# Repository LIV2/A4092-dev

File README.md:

# A4092

A modern successor to the A4091.

* TSSOP parts for smaller footprint
* Flash instead of EPROM
* CPLD instead of GALs
* Autoconfig moved into CPLD

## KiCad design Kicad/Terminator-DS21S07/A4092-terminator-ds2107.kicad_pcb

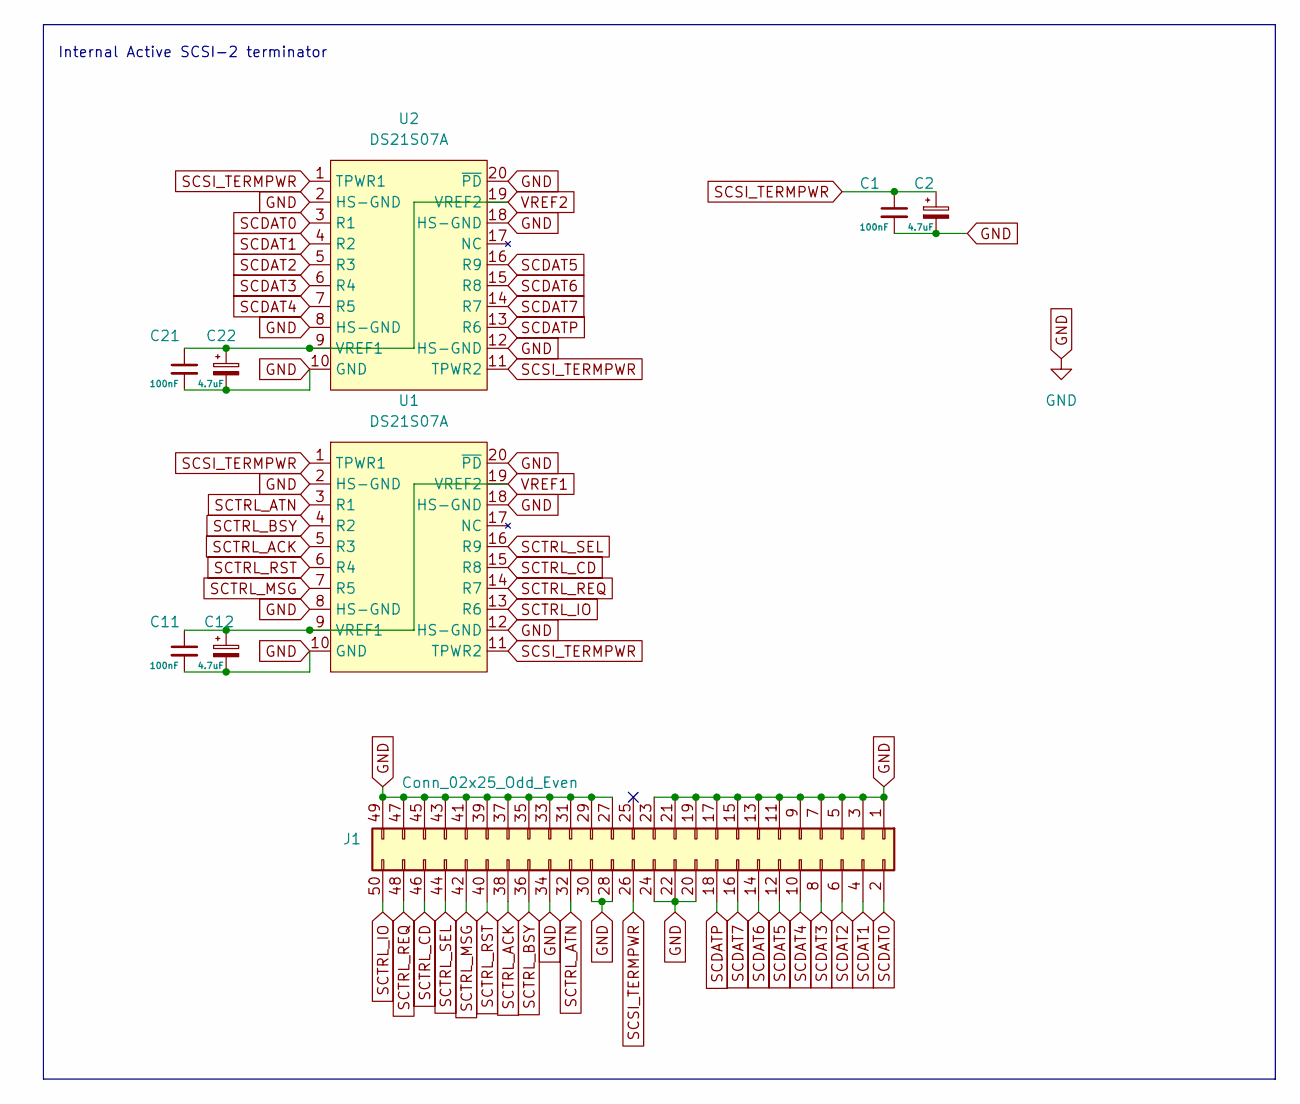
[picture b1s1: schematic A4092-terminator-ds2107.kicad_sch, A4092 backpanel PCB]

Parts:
C1, C11, C21: 100nF; C_0603_1608Metric_Pad1.08x0.95mm_HandSolder; LCSC Part # C14663
C2, C12, C22: 4.7uF; CP_EIA-3216-10_Kemet-I_HandSolder; LCSC Part # C7189
J1: Conn_02x25_Odd_Even; IDC-Header_2x25_P2.54mm_Horizontal; LCSC Part # C7430330
U1, U2: DS21S07A; TSSOP-20_4.4x6.5mm_P0.65mm; LCSC Part # C6602097

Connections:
GND: C1.2, C2.2, C11.2, C12.2, C21.2, C22.2, J1.1, J1.3, J1.5, J1.7, J1.9, J1.11, J1.13, J1.15, J1.17, J1.19, J1.20, J1.21, J1.22, J1.23, J1.24, J1.27, J1.28, J1.29, J1.30, J1.31, J1.33, J1.34, J1.35, J1.37, J1.39, J1.41, J1.43, J1.45, J1.47, J1.49, U1.2 (HS-GND), U1.8 (HS-GND), U1.10 (GND), U1.12 (HS-GND), U1.18 (HS-GND), U1.20 (~PD), U2.2 (HS-GND), U2.8 (HS-GND), U2.10 (GND), U2.12 (HS-GND), U2.18 (HS-GND), U2.20 (~PD)
SCDAT0: J1.2, U2.3 (R1)
SCDAT1: J1.4, U2.4 (R2)
SCDAT2: J1.6, U2.5 (R3)
SCDAT3: J1.8, U2.6 (R4)
SCDAT4: J1.10, U2.7 (R5)
SCDAT5: J1.12, U2.16 (R9)
SCDAT6: J1.14, U2.15 (R8)
SCDAT7: J1.16, U2.14 (R7)
SCDATP: J1.18, U2.13 (R6)
SCSI_TERMPWR: C1.1, C2.1, J1.26, U1.1 (TPWR1), U1.11 (TPWR2), U2.1 (TPWR1), U2.11 (TPWR2)
SCTRL_ACK: J1.38, U1.5 (R3)
SCTRL_ATN: J1.32, U1.3 (R1)
SCTRL_BSY: J1.36, U1.4 (R2)
SCTRL_CD: J1.46, U1.15 (R8)
SCTRL_IO: J1.50, U1.13 (R6)
SCTRL_MSG: J1.42, U1.7 (R5)
SCTRL_REQ: J1.48, U1.14 (R7)
SCTRL_RST: J1.40, U1.6 (R4)
SCTRL_SEL: J1.44, U1.16 (R9)
VREF1: C11.1, C12.1, U1.9 (VREF1), U1.19 (VREF2)
VREF2: C21.1, C22.1, U2.9 (VREF1), U2.19 (VREF2)

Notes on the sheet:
Internal Active SCSI-2 terminator

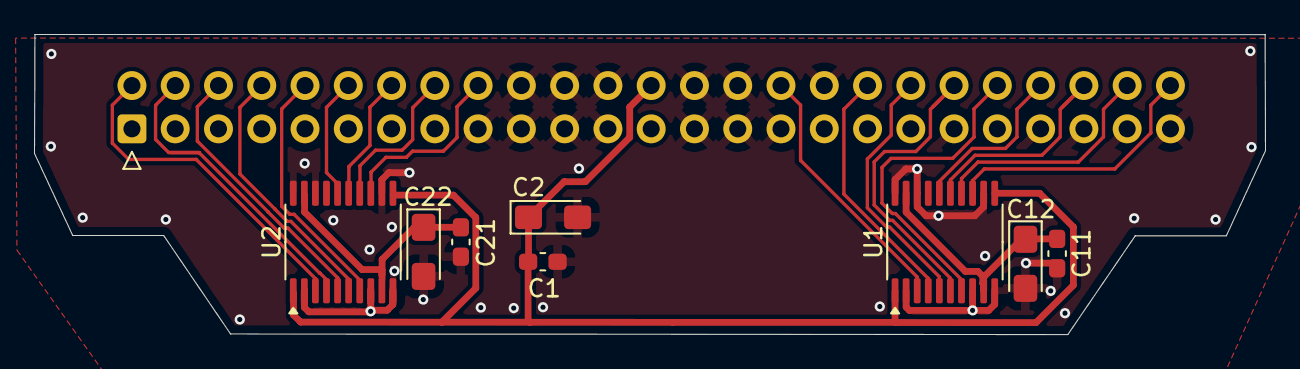
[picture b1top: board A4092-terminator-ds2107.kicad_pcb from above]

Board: 2 copper layers, 72.3 x 17.6 mm, 9 parts (0 on the bottom side), 22 nets.

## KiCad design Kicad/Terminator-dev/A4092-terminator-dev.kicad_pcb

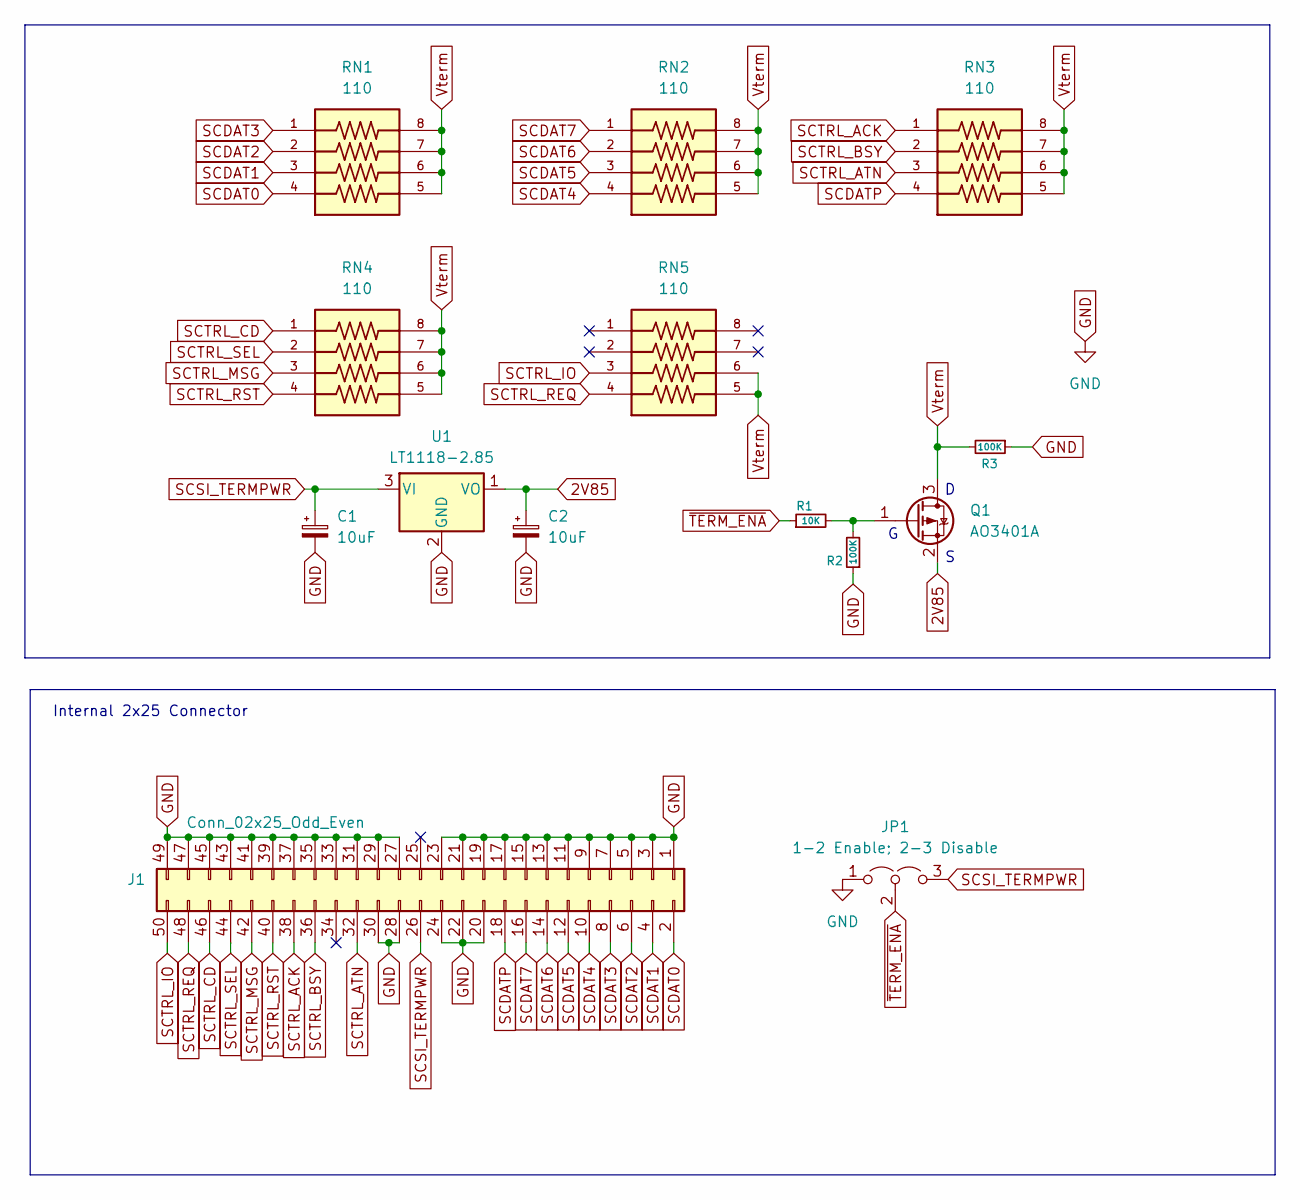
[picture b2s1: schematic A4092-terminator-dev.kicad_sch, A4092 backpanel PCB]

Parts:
C1, C2: 10uF; CP_EIA-2012-12_Kemet-R; LCSC Part # C7171
J1: Conn_02x25_Odd_Even; IDC-Header_2x25_P2.54mm_Horizontal; LCSC Part # C7430330
JP1: 1-2 Enable; 2-3 Disable; PinHeader_1x03_P2.00mm_Horizontal
Q1: AO3401A; SOT-23
R1: 10K; R_0603_1608Metric
R2, R3: 100K; R_0603_1608Metric
RN1, RN2, RN3, RN4, RN5: 110; BO_CAY16; PARTREV V.9; LCSC Part # C176176
U1: LT1118-2.85; SOT-223-3_TabPin2; LCSC Part # C2870974

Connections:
2V85: C2.1, Q1.2 (S), U1.1 (VO)
GND: C1.2, C2.2, J1.1, J1.3, J1.5, J1.7, J1.9, J1.11, J1.13, J1.15, J1.17, J1.19, J1.20, J1.21, J1.22, J1.23, J1.24, J1.27, J1.28, J1.29, J1.30, J1.31, J1.33, J1.35, J1.37, J1.39, J1.41, J1.43, J1.45, J1.47, J1.49, JP1.1 (A), R2.1, R3.1, U1.2 (GND)
unnamed: Q1.1 (G), R1.2, R2.2
SCDAT0: J1.2, RN1.4
SCDAT1: J1.4, RN1.3
SCDAT2: J1.6, RN1.2
SCDAT3: J1.8, RN1.1
SCDAT4: J1.10, RN2.4
SCDAT5: J1.12, RN2.3
SCDAT6: J1.14, RN2.2
SCDAT7: J1.16, RN2.1
SCDATP: J1.18, RN3.4
SCSI_TERMPWR: C1.1, J1.26, JP1.3 (B), U1.3 (VI)
SCTRL_ACK: J1.38, RN3.1
SCTRL_ATN: J1.32, RN3.3
SCTRL_BSY: J1.36, RN3.2
SCTRL_CD: J1.46, RN4.1
SCTRL_IO: J1.50, RN5.3
SCTRL_MSG: J1.42, RN4.3
SCTRL_REQ: J1.48, RN5.4
SCTRL_RST: J1.40, RN4.4
SCTRL_SEL: J1.44, RN4.2
Vterm: Q1.3 (D), R3.2, RN1.5, RN1.6, RN1.7, RN1.8, RN2.5, RN2.6, RN2.7, RN2.8, RN3.5, RN3.6, RN3.7, RN3.8, RN4.5, RN4.6, RN4.7, RN4.8, RN5.5, RN5.6
~TERM_ENA: JP1.2 (C), R1.1

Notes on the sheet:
Internal 2x25 Connector

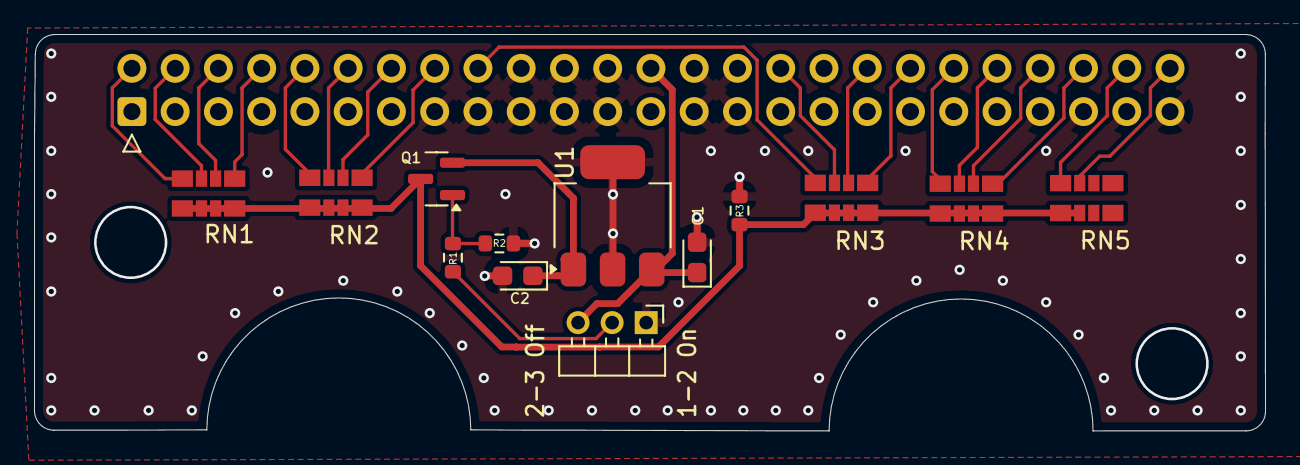
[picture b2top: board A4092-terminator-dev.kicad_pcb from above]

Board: 2 copper layers, 72.3 x 23.3 mm, 14 parts (0 on the bottom side), 24 nets.

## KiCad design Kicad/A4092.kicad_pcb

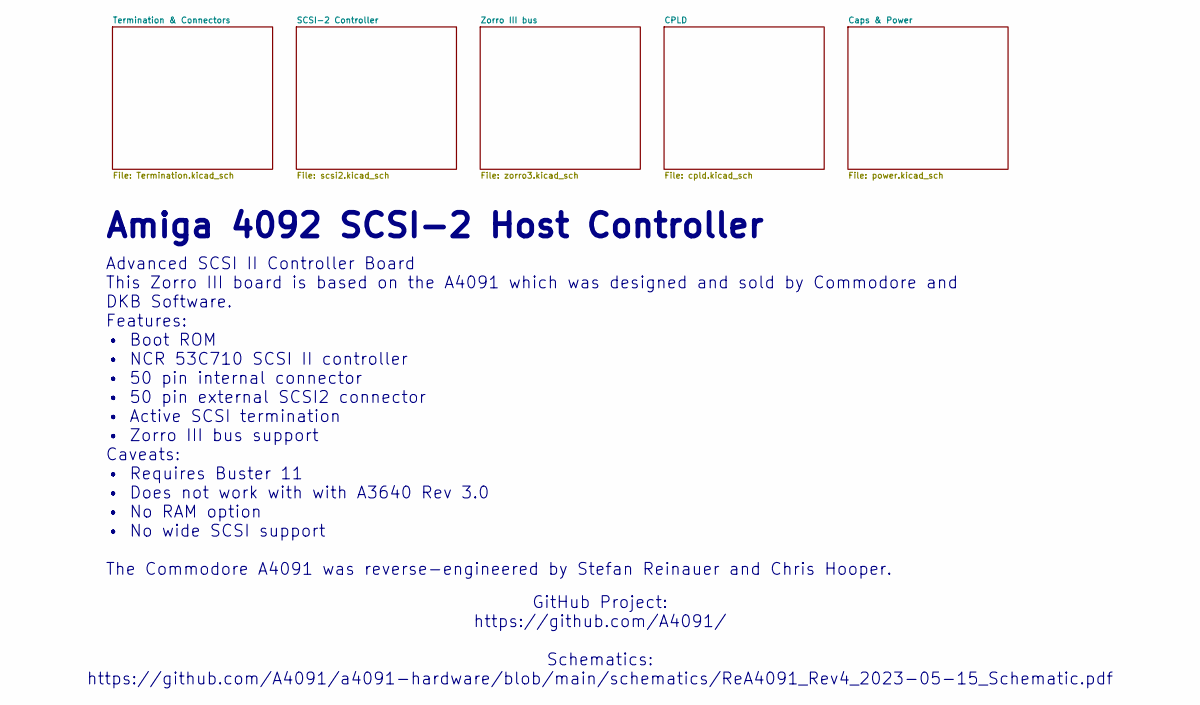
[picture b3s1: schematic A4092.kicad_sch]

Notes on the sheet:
Advanced SCSI II Controller Board This Zorro III board is based on the A4091 which was designed and sold by Commodore and DKB Software. Features: • Boot ROM • NCR 53C710 SCSI II controller • 50 pin internal connector • 50 pin external SCSI2 connector • Active SCSI termination • Zorro III bus suppor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
GitHub Project: https://github.com/A4091/ Schematics: https://github.com/A4091/a4091-hardware/blob/main/schematics/ReA4091_Rev4_2023-05-15_Schematic.pdf
Amiga 4092 SCSI-2 Host Controller

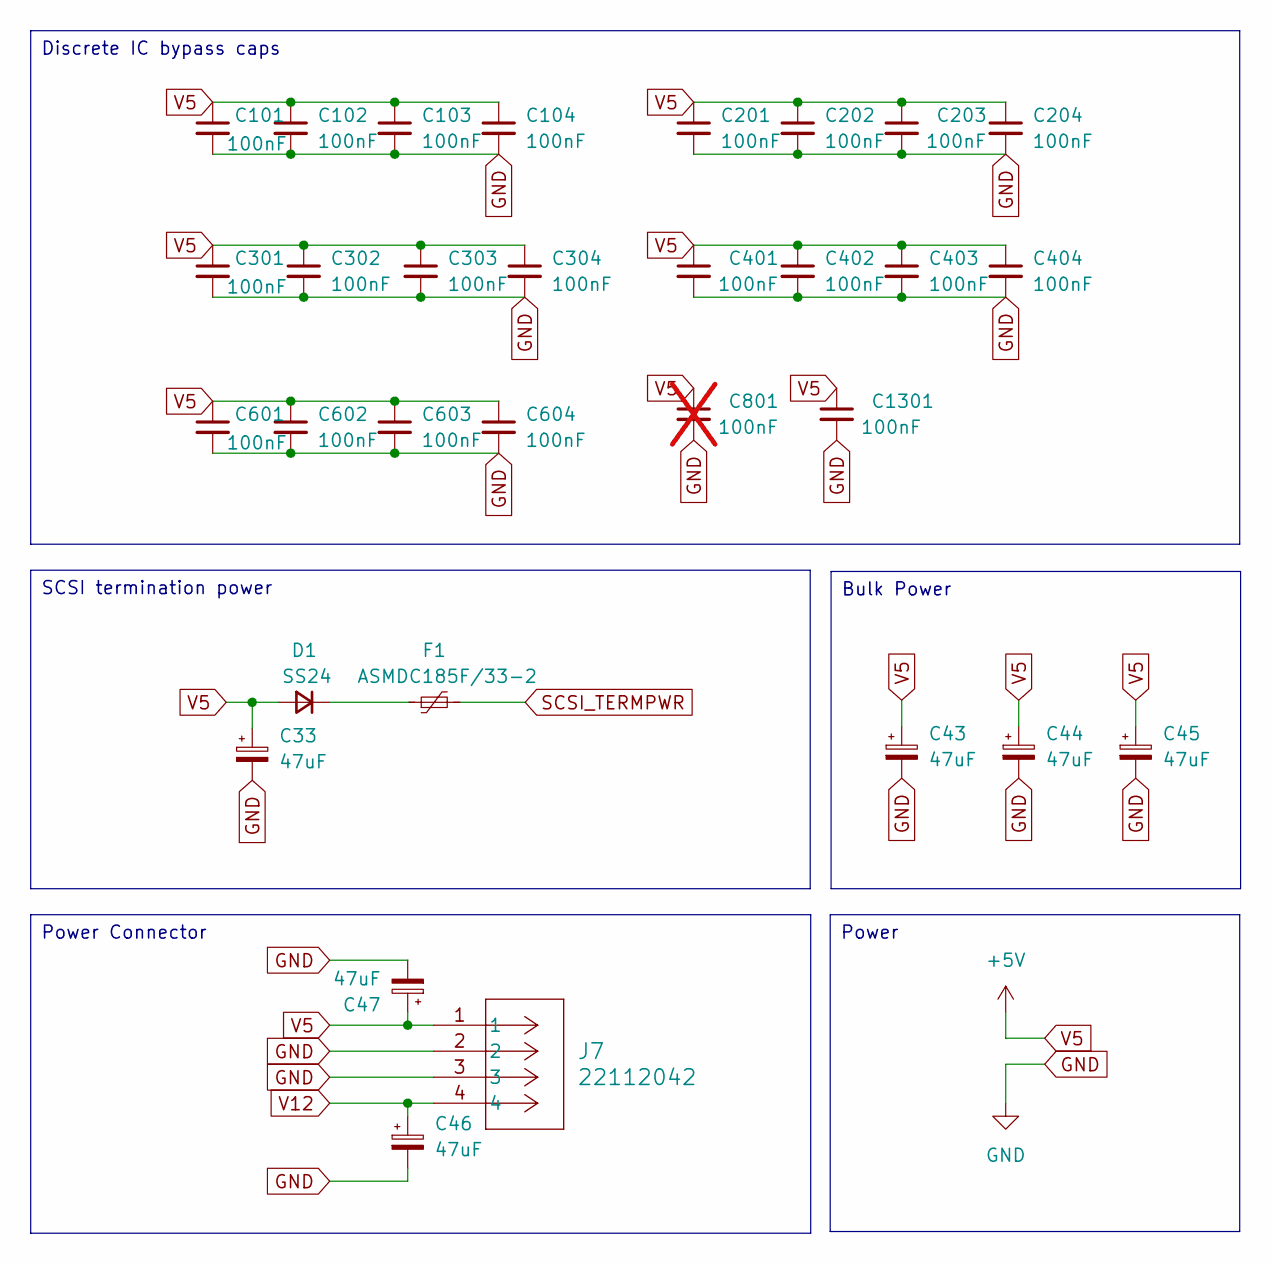
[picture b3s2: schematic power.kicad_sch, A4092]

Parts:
C33, C43, C44, C45, C46, C47: 47uF; CP_Elec_6.3x7.7; MPN KEMET/A765EB476M1ELAE040; LCSC Part # C369909
C101, C102, C103, C104, C201, C202, C203, C204, C301, C302, C303, C304, C401, C402, C403, C404, C601, C602, C603, C604, C1301: 100nF; C_0603_1608Metric_Pad1.08x0.95mm_HandSolder; LCSC Part # C14663
C801: 100nF; C_0603_1608Metric_Pad1.08x0.95mm_HandSolder; LCSC Part # C14663; not fitted
D1: SS24; D_SMA_Handsoldering; LCSC Part # C43381
F1: ASMDC185F/33-2; Fuse_2920_7451Metric_Pad2.10x5.45mm_HandSolder; LCSC Part # C135379
J7: 22112042; CONN_A-6373-04A_MOL; LCSC Part # C114123

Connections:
GND: C33.2, C43.2, C44.2, C45.2, C46.2, C47.2, C101.2, C102.2, C103.2, C104.2, C201.2, C202.2, C203.2, C204.2, C301.2, C302.2, C303.2, C304.2, C401.2, C402.2, C403.2, C404.2, C601.2, C602.2, C603.2, C604.2, C801.2, C1301.2, J7.2, J7.3; also elsewhere on the board
unnamed: D1.1 (K), F1.1
SCSI_TERMPWR: F1.2; also elsewhere on the board
V5: C33.1, C43.1, C44.1, C45.1, C47.1, C101.1, C102.1, C103.1, C104.1, C201.1, C202.1, C203.1, C204.1, C301.1, C302.1, C303.1, C304.1, C401.1, C402.1, C403.1, C404.1, C601.1, C602.1, C603.1, C604.1, C801.1, C1301.1, D1.2 (A), J7.1; also elsewhere on the board
V12: C46.1, J7.4; also elsewhere on the board

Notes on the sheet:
SCSI termination power
Power Connector
Discrete IC bypass caps
Bulk Power
Power

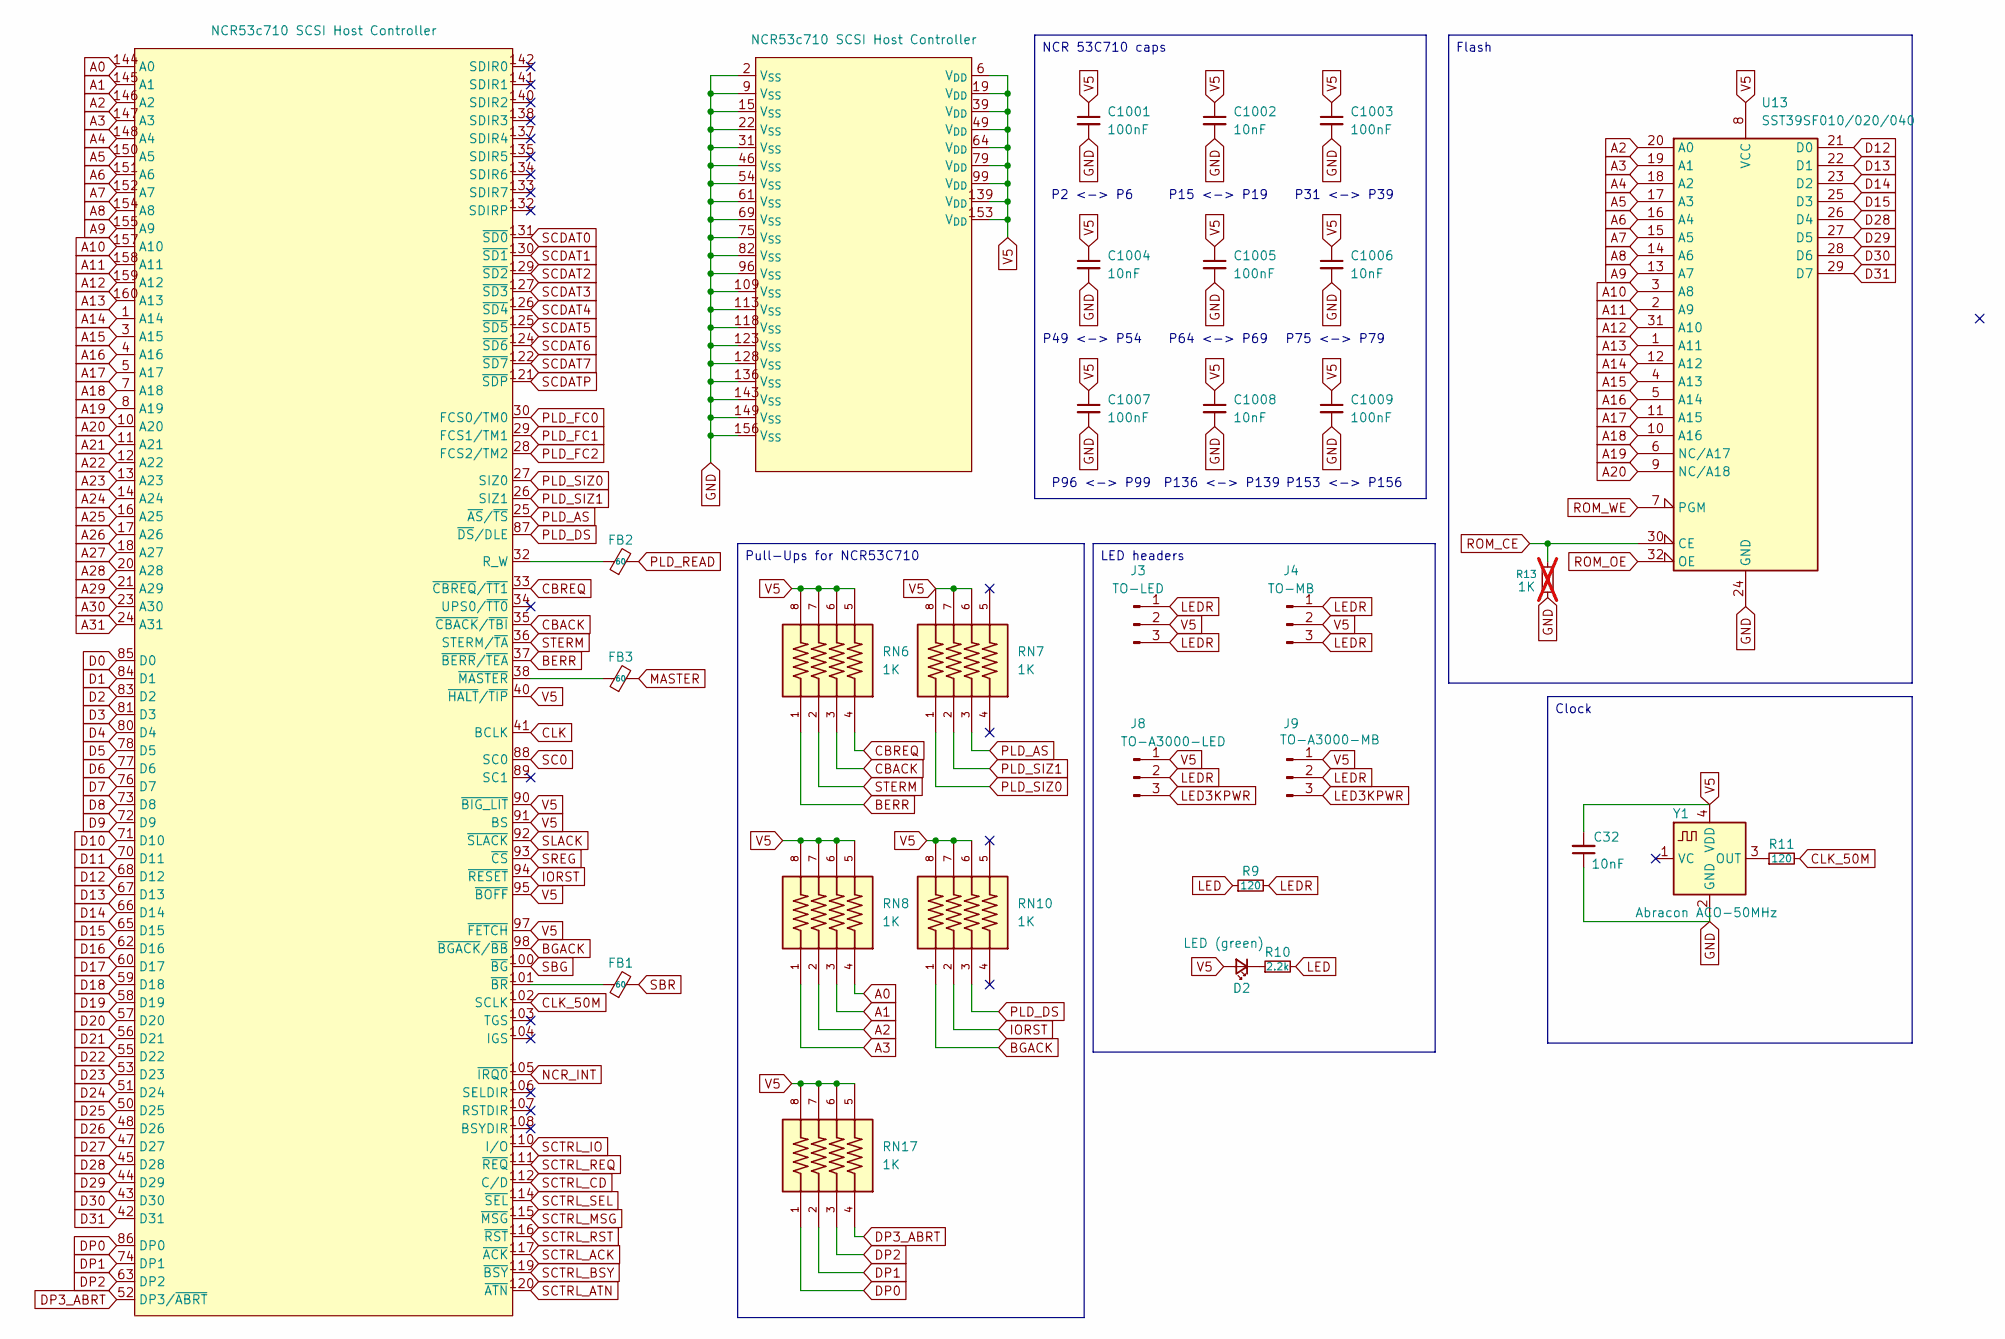
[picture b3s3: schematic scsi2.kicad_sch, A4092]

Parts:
C32, C1002, C1004, C1006, C1008: 10nF; C_0603_1608Metric_Pad1.08x0.95mm_HandSolder; LCSC Part # C100042
C1001, C1003, C1005, C1007, C1009: 100nF; C_0603_1608Metric_Pad1.08x0.95mm_HandSolder; LCSC Part # C14663
D2: LED (green); LED_0805_2012Metric; LCSC Part # C965821
FB1, FB2, FB3: 60; C_0603_1608Metric_Pad1.08x0.95mm_HandSolder; LCSC Part # C95177
J3: TO-LED; PinHeader_1x03_P2.54mm_Vertical; LCSC Part # C6332196
J4: TO-MB; PinHeader_1x03_P2.54mm_Vertical; LCSC Part # C6332196
J8: TO-A3000-LED; PinHeader_1x03_P2.54mm_Vertical; LCSC Part # C6332196
J9: TO-A3000-MB; PinHeader_1x03_P2.54mm_Vertical; LCSC Part # C6332196
R9: 120; R_0603_1608Metric; LCSC Part # C114640
R10: 2.2k; R_0603_1608Metric; LCSC Part # C114662
R11: 120; R_0603_1608Metric; LCSC Part # C95177
R13: 1K; R_0603_1608Metric; LCSC Part # C22548; not fitted
RN6, RN7, RN8, RN10, RN17: 1K; BO_CAY16; PARTREV V.9; LCSC Part # C784824
U10: NCR53c710 SCSI Host Controller; PQFP-160_28x28mm_P0.65mm; LCSC Part # C9900133089
U13: SST39SF010/020/040; TSSOP-32_8x11mm_P0.65mm; LCSC Part # C630569
Y1: Abracon ACO-50MHz; Oscillator_SMD_Fox_FT5H_5.0x3.2mm; LCSC Part # C7431196

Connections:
A0: RN8.4, U10.144 (A0); also elsewhere on the board
A1: RN8.3, U10.145 (A1); also elsewhere on the board
A2: RN8.2, U10.146 (A2), U13.20 (A0); also elsewhere on the board
A3: RN8.1, U10.147 (A3), U13.19 (A1); also elsewhere on the board
A4: U10.148 (A4), U13.18 (A2); also elsewhere on the board
A5: U10.150 (A5), U13.17 (A3); also elsewhere on the board
A6: U10.151 (A6), U13.16 (A4); also elsewhere on the board
A7: U10.152 (A7), U13.15 (A5); also elsewhere on the board
A8: U10.154 (A8), U13.14 (A6); also elsewhere on the board
A9: U10.155 (A9), U13.13 (A7); also elsewhere on the board
A10: U10.157 (A10), U13.3 (A8); also elsewhere on the board
A11: U10.158 (A11), U13.2 (A9); also elsewhere on the board
A12: U10.159 (A12), U13.31 (A10); also elsewhere on the board
A13: U10.160 (A13), U13.1 (A11); also elsewhere on the board
A14: U10.1 (A14), U13.12 (A12); also elsewhere on the board
A15: U10.3 (A15), U13.4 (A13); also elsewhere on the board
A16: U10.4 (A16), U13.5 (A14); also elsewhere on the board
A17: U10.5 (A17), U13.11 (A15); also elsewhere on the board
A18: U10.7 (A18), U13.10 (A16); also elsewhere on the board
A19: U10.8 (A19), U13.6 (NC/A17); also elsewhere on the board
A20: U10.10 (A20), U13.9 (NC/A18); also elsewhere on the board
A21: U10.11 (A21); also elsewhere on the board
A22: U10.12 (A22); also elsewhere on the board
A23: U10.13 (A23); also elsewhere on the board
A24: U10.14 (A24); also elsewhere on the board
A25: U10.16 (A25); also elsewhere on the board
A26: U10.17 (A26); also elsewhere on the board
A27: U10.18 (A27); also elsewhere on the board
A28: U10.20 (A28); also elsewhere on the board
A29: U10.21 (A29); also elsewhere on the board
A30: U10.23 (A30); also elsewhere on the board
A31: U10.24 (A31); also elsewhere on the board
BERR: RN6.1, U10.37 (~BERR/~TEA); also elsewhere on the board
BGACK: RN10.1, U10.98 (~BGACK/~BB)
CBACK: RN6.3, U10.35 (~CBACK/~TBI); also elsewhere on the board
CBREQ: RN6.4, U10.33 (~CBREQ/~TT1); also elsewhere on the board
CLK: U10.41 (BCLK); also elsewhere on the board
CLK_50M: R11.2, U10.102 (SCLK); also elsewhere on the board
D0: U10.85 (D0); also elsewhere on the board
D1: U10.84 (D1); also elsewhere on the board
D2: U10.83 (D2); also elsewhere on the board
D3: U10.81 (D3); also elsewhere on the board
D4: U10.80 (D4); also elsewhere on the board
D5: U10.78 (D5); also elsewhere on the board
D6: U10.77 (D6); also elsewhere on the board
D7: U10.76 (D7); also elsewhere on the board
D8: U10.73 (D8); also elsewhere on the board
D9: U10.72 (D9); also elsewhere on the board
D10: U10.71 (D10); also elsewhere on the board
D11: U10.70 (D11); also elsewhere on the board
D12: U10.68 (D12), U13.21 (D0); also elsewhere on the board
D13: U10.67 (D13), U13.22 (D1); also elsewhere on the board
D14: U10.66 (D14), U13.23 (D2); also elsewhere on the board
D15: U10.65 (D15), U13.25 (D3); also elsewhere on the board
D16: U10.62 (D16); also elsewhere on the board
D17: U10.60 (D17); also elsewhere on the board
D18: U10.59 (D18); also elsewhere on the board
D19: U10.58 (D19); also elsewhere on the board
D20: U10.57 (D20); also elsewhere on the board
D21: U10.56 (D21); also elsewhere on the board
D22: U10.55 (D22); also elsewhere on the board
D23: U10.53 (D23); also elsewhere on the board
D24: U10.51 (D24); also elsewhere on the board
D25: U10.50 (D25); also elsewhere on the board
D26: U10.48 (D26); also elsewhere on the board
D27: U10.47 (D27); also elsewhere on the board
D28: U10.45 (D28), U13.26 (D4); also elsewhere on the board
D29: U10.44 (D29), U13.27 (D5); also elsewhere on the board
D30: U10.43 (D30), U13.28 (D6); also elsewhere on the board
D31: U10.42 (D31), U13.29 (D7); also elsewhere on the board
DP0: RN17.1, U10.86 (DP0)
DP1: RN17.2, U10.74 (DP1)
DP2: RN17.3, U10.63 (DP2)
DP3_ABRT: RN17.4, U10.52 (DP3/~ABRT)
GND: C32.1, C1001.2, C1002.2, C1003.2, C1004.2, C1005.2, C1006.2, C1007.2, C1008.2, C1009.2, R13.2, U10.2 (V_{SS}), U10.9 (V_{SS}), U10.15 (V_{SS}), U10.22 (V_{SS}), U10.31 (V_{SS}), U10.46 (V_{SS}), U10.54 (V_{SS}), U10.61 (V_{SS}), U10.69 (V_{SS}), U10.75 (V_{SS}), U10.82 (V_{SS}), U10.96 (V_{SS}), U10.109 (V_{SS}), U10.113 (V_{SS}), U10.118 (V_{SS}), U10.123 (V_{SS}), U10.128 (V_{SS}), U10.136 (V_{SS}), U10.143 (V_{SS}), U10.149 (V_{SS}), U10.156 (V_{SS}), U13.24 (GND), Y1.2 (GND); also elsewhere on the board
IORST: RN10.2, U10.94 (~RESET); also elsewhere on the board
LED: R9.1, R10.2; also elsewhere on the board
LED3KPWR: J8.3, J9.3
LEDR: J3.1, J3.3, J4.1, J4.3, J8.2, J9.2, R9.2
MASTER: FB3.2; also elsewhere on the board
NCR_INT: U10.105 (~IRQ0); also elsewhere on the board
unnamed: D2.1 (K), R10.1
unnamed: FB2.1, U10.32 (R_W)
unnamed: FB1.1, U10.101 (~BR)
unnamed: FB3.1, U10.38 (~MASTER)
unnamed: R11.1, Y1.3 (OUT)
PLD_AS: RN7.3, U10.25 (~AS/~TS); also elsewhere on the board
PLD_DS: RN10.3, U10.87 (~DS/DLE); also elsewhere on the board
PLD_FC0: U10.30 (FCS0/TM0); also elsewhere on the board
PLD_FC1: U10.29 (FCS1/TM1); also elsewhere on the board
PLD_FC2: U10.28 (FCS2/TM2); also elsewhere on the board
PLD_READ: FB2.2; also elsewhere on the board
PLD_SIZ0: RN7.1, U10.27 (SIZ0); also elsewhere on the board
PLD_SIZ1: RN7.2, U10.26 (SIZ1); also elsewhere on the board
ROM_CE: R13.1, U13.30 (CE); also elsewhere on the board
ROM_OE: U13.32 (OE); also elsewhere on the board
ROM_WE: U13.7 (PGM); also elsewhere on the board
SBG: U10.100 (~BG); also elsewhere on the board
SBR: FB1.2; also elsewhere on the board
SC0: U10.88 (SC0); also elsewhere on the board
SCDAT0: U10.131 (~SD0); also elsewhere on the board
SCDAT1: U10.130 (~SD1); also elsewhere on the board
SCDAT2: U10.129 (~SD2); also elsewhere on the board
SCDAT3: U10.127 (~SD3); also elsewhere on the board
SCDAT4: U10.126 (~SD4); also elsewhere on the board
SCDAT5: U10.125 (~SD5); also elsewhere on the board
SCDAT6: U10.124 (~SD6); also elsewhere on the board
SCDAT7: U10.122 (~SD7); also elsewhere on the board
SCDATP: U10.121 (~SDP); also elsewhere on the board
SCTRL_ACK: U10.117 (~ACK); also elsewhere on the board
SCTRL_ATN: U10.120 (~ATN); also elsewhere on the board
SCTRL_BSY: U10.119 (~BSY); also elsewhere on the board
SCTRL_CD: U10.112 (C/D); also elsewhere on the board
SCTRL_IO: U10.110 (I/O); also elsewhere on the board
SCTRL_MSG: U10.115 (~MSG); also elsewhere on the board
SCTRL_REQ: U10.111 (~REQ); also elsewhere on the board
SCTRL_RST: U10.116 (~RST); also elsewhere on the board
SCTRL_SEL: U10.114 (~SEL); also elsewhere on the board
SLACK: U10.92 (~SLACK); also elsewhere on the board
SREG: U10.93 (~CS); also elsewhere on the board
STERM: RN6.2, U10.36 (STERM/~TA); also elsewhere on the board
V5: C32.2, C1001.1, C1002.1, C1003.1, C1004.1, C1005.1, C1006.1, C1007.1, C1008.1, C1009.1, D2.2 (A), J3.2, J4.2, J8.1, J9.1, RN6.5, RN6.6, RN6.7, RN6.8, RN7.6, RN7.7, RN7.8, RN8.5, RN8.6, RN8.7, RN8.8, RN10.6, RN10.7, RN10.8, RN17.5, RN17.6, RN17.7, RN17.8, U10.6 (V_{DD}), U10.19 (V_{DD}), U10.39 (V_{DD}), U10.40 (~HALT/~TIP), U10.49 (V_{DD}), U10.64 (V_{DD}), U10.79 (V_{DD}), U10.90 (~BIG_LIT), U10.91 (BS), U10.95 (~BOFF), U10.97 (~FETCH), U10.99 (V_{DD}), U10.139 (V_{DD}), U10.153 (V_{DD}), U13.8 (VCC), Y1.4 (VDD); also elsewhere on the board

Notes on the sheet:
P2 <-> P6
P96 <-> P99
P49 <-> P54
P136 <-> P139
P153 <-> P156
P31 <-> P39
P64 <-> P69
P15 <-> P19
P75 <-> P79
LED headers
NCR 53C710 caps
Clock
Flash
Pull-Ups for NCR53C710

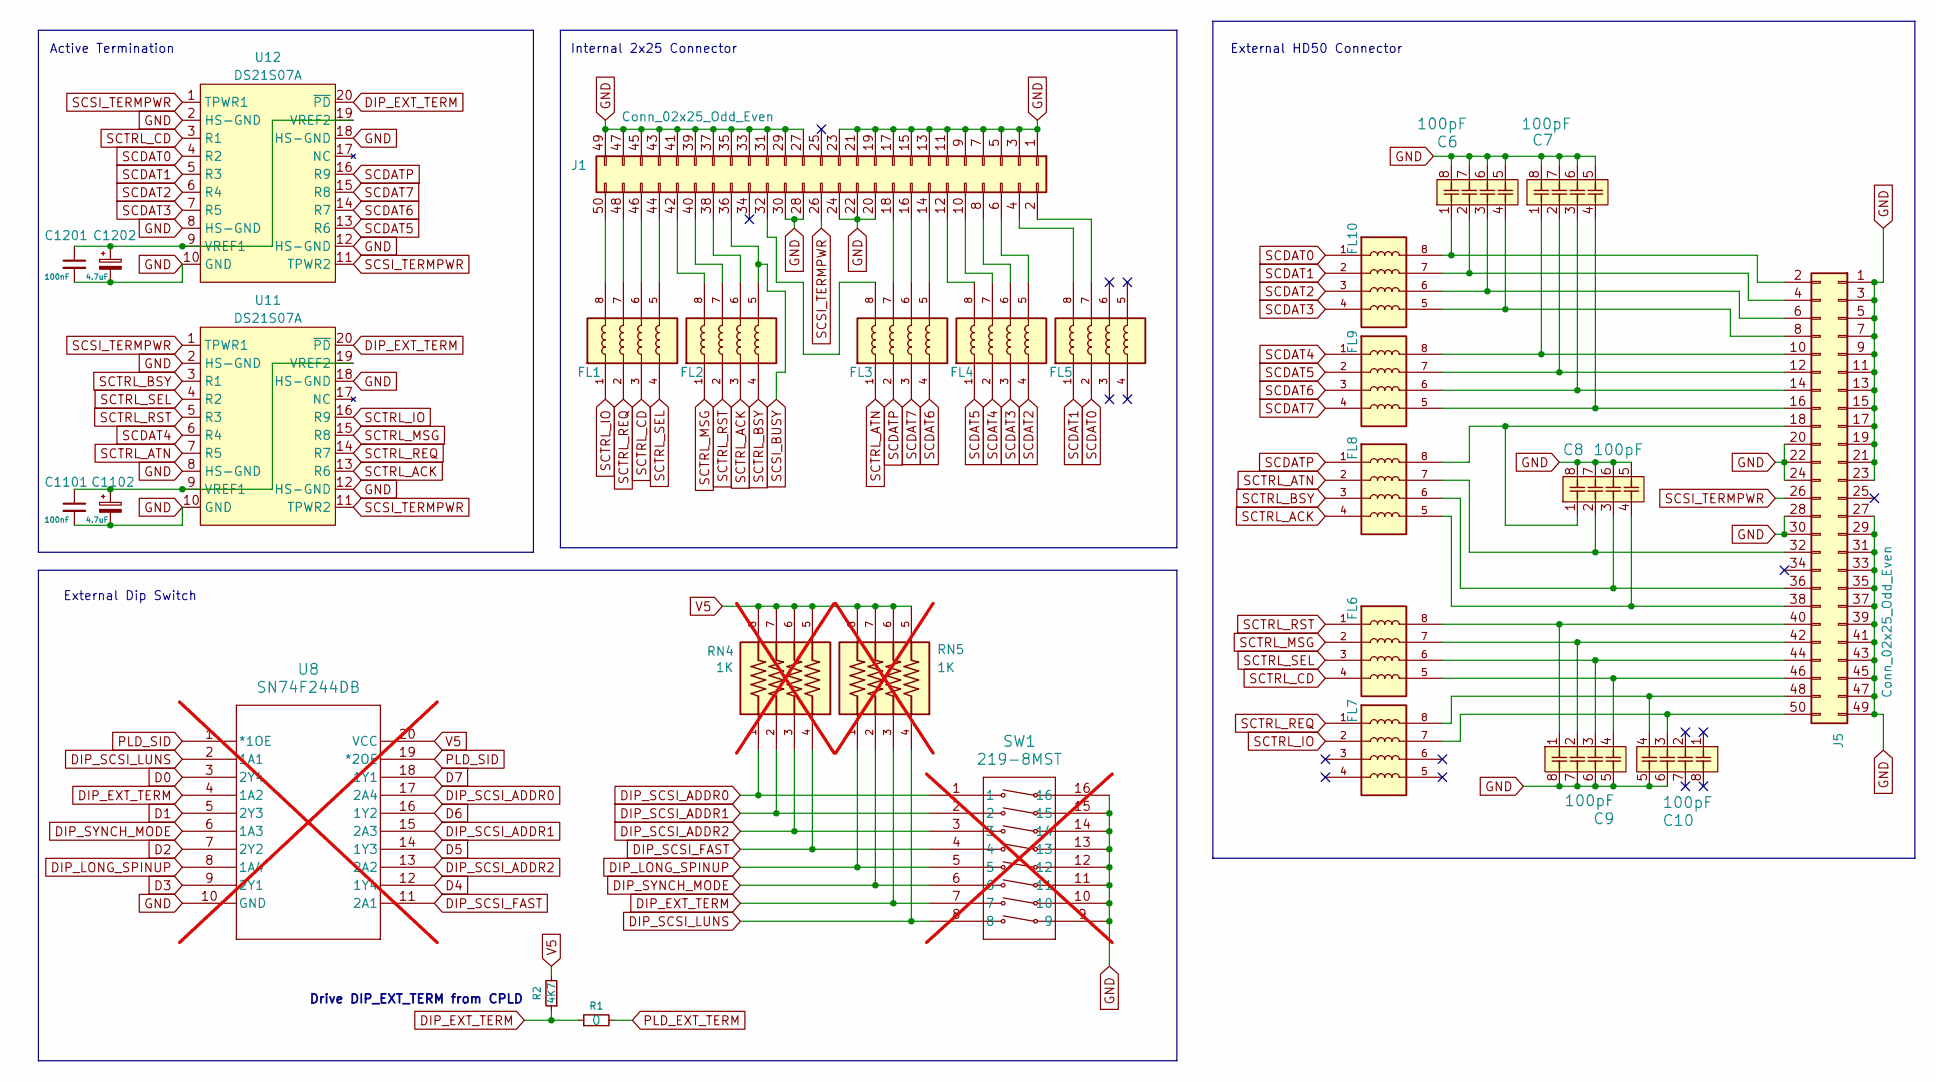
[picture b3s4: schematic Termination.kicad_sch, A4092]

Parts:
C6, C7, C8, C9, C10: 100pF; CAP_CA0612_3P2X1P6_YAG; LCSC Part # C576629
C1101, C1201: 100nF; C_0603_1608Metric_Pad1.08x0.95mm_HandSolder; LCSC Part # C14663
C1102, C1202: 4.7uF; CP_EIA-3216-10_Kemet-I_HandSolder; LCSC Part # C7189
FL1, FL2, FL3, FL4, FL5, FL6, FL7, FL8, FL9, FL10: DA1206D600R-10; FB_DA1206D600R-10; PARTREV F; DigiKey_Part_Number 240-2539-2-ND
J1, J5: Conn_02x25_Odd_Even; IDC-Header_2x25_P2.54mm_Vertical; LCSC Part # C221059
R1: 0; R_0603_1608Metric_Pad0.98x0.95mm_HandSolder; LCSC Part # C95177
R2: 4K7; R_0603_1608Metric_Pad0.98x0.95mm_HandSolder; LCSC Part # C99782
RN4, RN5: 1K; BO_CAY16; PARTREV V.9; LCSC Part # C784824; not fitted
SW1: 219-8MST; SO16_219-8_CTS; LCSC Part # C2842674; not fitted
U8: SN74F244DB; DB20; LCSC Part # C543080; not fitted
U11, U12: DS21S07A; TSSOP-20_4.4x6.5mm_P0.65mm; LCSC Part # C6602097

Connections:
D0: U8.3 (2Y4); also elsewhere on the board
D1: U8.5 (2Y3); also elsewhere on the board
D2: U8.7 (2Y2); also elsewhere on the board
D3: U8.9 (2Y1); also elsewhere on the board
D4: U8.12 (1Y4); also elsewhere on the board
D5: U8.14 (1Y3); also elsewhere on the board
D6: U8.16 (1Y2); also elsewhere on the board
D7: U8.18 (1Y1); also elsewhere on the board
DIP_EXT_TERM: R1.1, R2.1, RN5.3, SW1.7, U8.4 (1A2), U11.20 (~PD), U12.20 (~PD)
DIP_LONG_SPINUP: RN5.1, SW1.5, U8.8 (1A4)
DIP_SCSI_ADDR0: RN4.1, SW1.1, U8.17 (2A4)
DIP_SCSI_ADDR1: RN4.2, SW1.2, U8.15 (2A3)
DIP_SCSI_ADDR2: RN4.3, SW1.3, U8.13 (2A2)
DIP_SCSI_FAST: RN4.4, SW1.4, U8.11 (2A1)
DIP_SCSI_LUNS: RN5.4, SW1.8, U8.2 (1A1)
DIP_SYNCH_MODE: RN5.2, SW1.6, U8.6 (1A3)
GND: C6.5, C6.6, C6.7, C6.8, C7.5, C7.6, C7.7, C7.8, C8.5, C8.6, C8.7, C8.8, C9.5, C9.6, C9.7, C9.8, C10.5, C10.6, C1101.2, C1102.2, C1201.2, C1202.2, J1.1, J1.3, J1.5, J1.7, J1.9, J1.11, J1.13, J1.15, J1.17, J1.19, J1.20, J1.21, J1.22, J1.23, J1.24, J1.27, J1.28, J1.29, J1.30, J1.31, J1.33, J1.35, J1.37, J1.39, J1.41, J1.43, J1.45, J1.47, J1.49, J5.1, J5.3, J5.5, J5.7, J5.9, J5.11, J5.13, J5.15, J5.17, J5.19, J5.20, J5.21, J5.22, J5.23, J5.24, J5.27, J5.28, J5.29, J5.30, J5.31, J5.33, J5.35, J5.37, J5.39, J5.41, J5.43, J5.45, J5.47, J5.49, SW1.9, SW1.10, SW1.11, SW1.12, SW1.13, SW1.14, SW1.15, SW1.16, U8.10 (GND), U11.2 (HS-GND), U11.8 (HS-GND), U11.10 (GND), U11.12 (HS-GND), U11.18 (HS-GND), U12.2 (HS-GND), U12.8 (HS-GND), U12.10 (GND), U12.12 (HS-GND), U12.18 (HS-GND); also elsewhere on the board
unnamed: FL5.7, J1.2
unnamed: FL5.8, J1.4
unnamed: FL4.5, J1.6
unnamed: FL4.6, J1.8
unnamed: FL4.7, J1.10
unnamed: FL4.8, J1.12
unnamed: FL3.5, J1.14
unnamed: FL3.6, J1.16
unnamed: FL3.7, J1.18
unnamed: FL3.8, J1.32
unnamed: FL2.6, J1.38
unnamed: FL2.7, J1.40
unnamed: FL2.8, J1.42
unnamed: FL1.5, J1.44
unnamed: FL1.6, J1.46
unnamed: FL1.7, J1.48
unnamed: FL1.8, J1.50
unnamed: C6.1, FL10.8, J5.2
unnamed: C6.2, FL10.7, J5.4
unnamed: C6.3, FL10.6, J5.6
unnamed: C6.4, FL10.5, J5.8
unnamed: C7.1, FL9.8, J5.10
unnamed: C7.2, FL9.7, J5.12
unnamed: C7.3, FL9.6, J5.14
unnamed: C7.4, FL9.5, J5.16
unnamed: C8.1, FL8.8, J5.18
unnamed: C8.2, FL8.7, J5.32
unnamed: C8.3, FL8.6, J5.36
unnamed: C8.4, FL8.5, J5.38
unnamed: C9.1, FL6.8, J5.40
unnamed: C9.2, FL6.7, J5.42
unnamed: C9.3, FL6.6, J5.44
unnamed: C9.4, FL6.5, J5.46
unnamed: C10.4, FL7.8, J5.48
unnamed: C10.3, FL7.7, J5.50
unnamed: C1101.1, C1102.1, U11.9 (VREF1), U11.19 (VREF2)
unnamed: C1201.1, C1202.1, U12.9 (VREF1), U12.19 (VREF2)
PLD_EXT_TERM: R1.2; also elsewhere on the board
PLD_SID: U8.1 (*1OE), U8.19 (*2OE); also elsewhere on the board
SCDAT0: FL5.2, FL10.1, U12.4 (R2); also elsewhere on the board
SCDAT1: FL5.1, FL10.2, U12.5 (R3); also elsewhere on the board
SCDAT2: FL4.4, FL10.3, U12.6 (R4); also elsewhere on the board
SCDAT3: FL4.3, FL10.4, U12.7 (R5); also elsewhere on the board
SCDAT4: FL4.2, FL9.1, U11.6 (R4); also elsewhere on the board
SCDAT5: FL4.1, FL9.2, U12.13 (R6); also elsewhere on the board
SCDAT6: FL3.4, FL9.3, U12.14 (R7); also elsewhere on the board
SCDAT7: FL3.3, FL9.4, U12.15 (R8); also elsewhere on the board
SCDATP: FL3.2, FL8.1, U12.16 (R9); also elsewhere on the board
SCSI_BUSY: FL2.5, J1.36; also elsewhere on the board
SCSI_TERMPWR: J1.26, J5.26, U11.1 (TPWR1), U11.11 (TPWR2), U12.1 (TPWR1), U12.11 (TPWR2); also elsewhere on the board
SCTRL_ACK: FL2.3, FL8.4, U11.13 (R6); also elsewhere on the board
SCTRL_ATN: FL3.1, FL8.2, U11.7 (R5); also elsewhere on the board
SCTRL_BSY: FL2.4, FL8.3, U11.3 (R1); also elsewhere on the board
SCTRL_CD: FL1.3, FL6.4, U12.3 (R1); also elsewhere on the board
SCTRL_IO: FL1.1, FL7.2, U11.16 (R9); also elsewhere on the board
SCTRL_MSG: FL2.1, FL6.2, U11.15 (R8); also elsewhere on the board
SCTRL_REQ: FL1.2, FL7.1, U11.14 (R7); also elsewhere on the board
SCTRL_RST: FL2.2, FL6.1, U11.5 (R3); also elsewhere on the board
SCTRL_SEL: FL1.4, FL6.3, U11.4 (R2); also elsewhere on the board
V5: R2.2, RN4.5, RN4.6, RN4.7, RN4.8, RN5.5, RN5.6, RN5.7, RN5.8, U8.20 (VCC); also elsewhere on the board

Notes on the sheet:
Active Termination
Drive DIP_EXT_TERM from CPLD
Internal 2x25 Connector
External HD50 Connector
External Dip Switch
